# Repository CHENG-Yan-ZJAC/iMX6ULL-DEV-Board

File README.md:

# iMX6ULL-DEV-Board

iMX6ULL-DEV-Board is a development board based on NXP i.MX6ULL. It is composed of core board and carrier board. The boards were developed in KiCad 8.0.

## Core Board
* i.MX6ULL, MCIMX6Y2CVM08AB, ARM Cortex-A7, 798MHz.
* Samsung, KLM8G1GETF-B041, 8GB eMMC.
* Micro, MT41K256M16, DDR3L, 512MB.
* DDR4 edge connector.

## Carrier Board
* micro SD x 1, 4-bit width.
* LCD.
* CSI.
* UART1, UART2.
* USB1: used as power and flash the eMMC.
* USB2: expand to 4 USB Type-A by USB Hub (GENESYS GL850G-HHY22).
* ENET1, ENET2: PHY SMSC LAN8720A-CP-TR.
* GPIO.

## How to use
* Connect the J2 (upright corner marked "Power Download") to 5V by a Type-C line.
* Connect the Type-C (the 2nd Type-C connector marked "UART1") to PC, it is the console.
* Insert micro SD to slot (downright corner marked "micro SD").
* Set the code switch to 1 0 0 0, boot from micro SD.
* Swith on (upright corner marked "ON OFF").

## Contact:
Feel free to contact me yan.cheng@hnautocontrol.com.

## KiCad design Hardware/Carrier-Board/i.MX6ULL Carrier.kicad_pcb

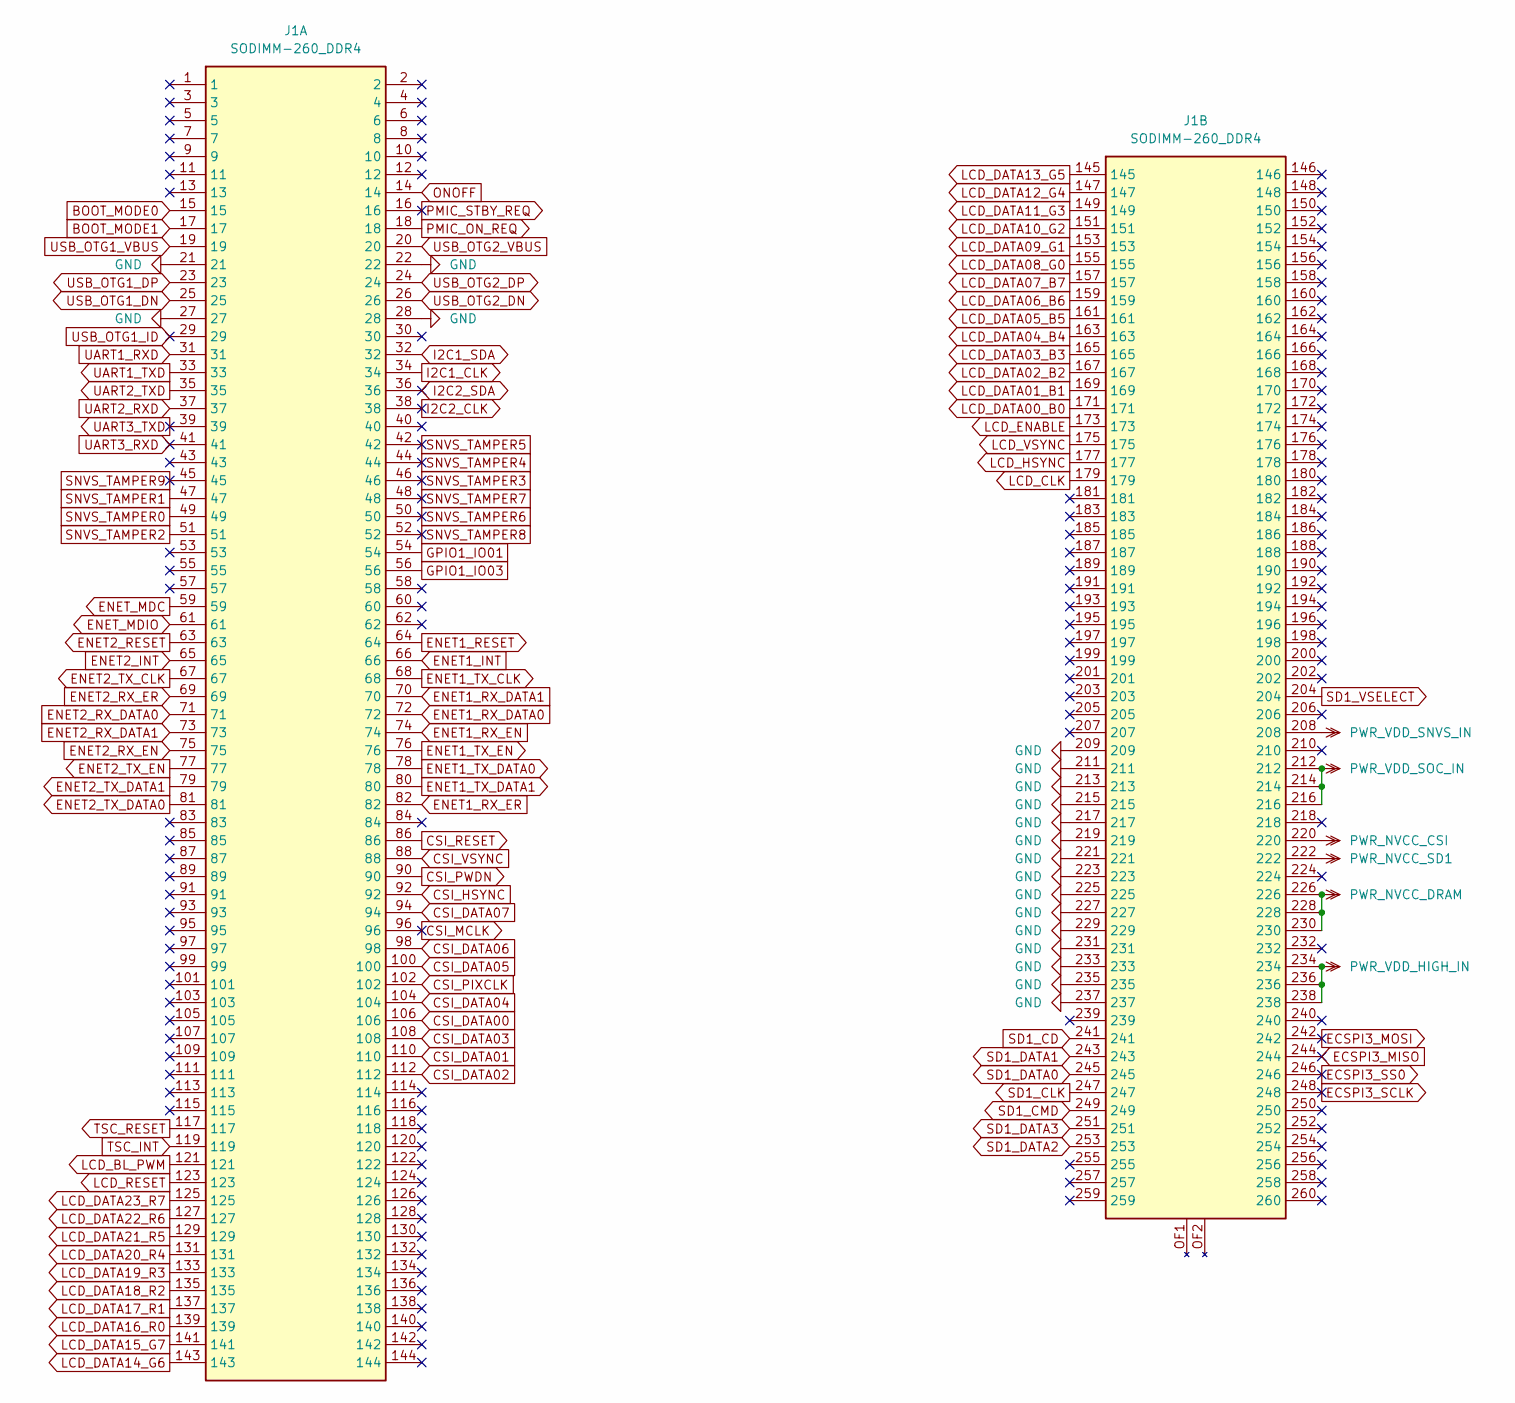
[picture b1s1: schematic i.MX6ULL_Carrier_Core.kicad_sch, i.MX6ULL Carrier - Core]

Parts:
J1: SODIMM-260_DDR4; SODIMM-260_DDR4_Card_slot

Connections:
BOOT_MODE0: J1.15; also elsewhere on the board
BOOT_MODE1: J1.17; also elsewhere on the board
CSI_DATA00: J1.106; also elsewhere on the board
CSI_DATA01: J1.110; also elsewhere on the board
CSI_DATA02: J1.112; also elsewhere on the board
CSI_DATA03: J1.108; also elsewhere on the board
CSI_DATA04: J1.104; also elsewhere on the board
CSI_DATA05: J1.100; also elsewhere on the board
CSI_DATA06: J1.98; also elsewhere on the board
CSI_DATA07: J1.94; also elsewhere on the board
CSI_HSYNC: J1.92; also elsewhere on the board
CSI_MCLK: J1.96
CSI_PIXCLK: J1.102; also elsewhere on the board
CSI_PWDN: J1.90; also elsewhere on the board
CSI_RESET: J1.86; also elsewhere on the board
CSI_VSYNC: J1.88; also elsewhere on the board
ECSPI3_MISO: J1.244
ECSPI3_MOSI: J1.242
ECSPI3_SCLK: J1.248
ECSPI3_SS0: J1.246
ENET1_INT: J1.66; also elsewhere on the board
ENET1_RESET: J1.64; also elsewhere on the board
ENET1_RX_DATA0: J1.72; also elsewhere on the board
ENET1_RX_DATA1: J1.70; also elsewhere on the board
ENET1_RX_EN: J1.74; also elsewhere on the board
ENET1_RX_ER: J1.82; also elsewhere on the board
ENET1_TX_CLK: J1.68; also elsewhere on the board
ENET1_TX_DATA0: J1.78; also elsewhere on the board
ENET1_TX_DATA1: J1.80; also elsewhere on the board
ENET1_TX_EN: J1.76; also elsewhere on the board
ENET2_INT: J1.65; also elsewhere on the board
ENET2_RESET: J1.63; also elsewhere on the board
ENET2_RX_DATA0: J1.71; also elsewhere on the board
ENET2_RX_DATA1: J1.73; also elsewhere on the board
ENET2_RX_EN: J1.75; also elsewhere on the board
ENET2_RX_ER: J1.69; also elsewhere on the board
ENET2_TX_CLK: J1.67; also elsewhere on the board
ENET2_TX_DATA0: J1.81; also elsewhere on the board
ENET2_TX_DATA1: J1.79; also elsewhere on the board
ENET2_TX_EN: J1.77; also elsewhere on the board
ENET_MDC: J1.59; also elsewhere on the board
ENET_MDIO: J1.61; also elsewhere on the board
GND: J1.21, J1.22, J1.27, J1.28, J1.209, J1.211, J1.213, J1.215, J1.217, J1.219, J1.221, J1.223, J1.225, J1.227, J1.229, J1.231, J1.233, J1.235, J1.237; also elsewhere on the board
GPIO1_IO01: J1.54; also elsewhere on the board
GPIO1_IO03: J1.56; also elsewhere on the board
I2C1_CLK: J1.34; also elsewhere on the board
I2C1_SDA: J1.32; also elsewhere on the board
I2C2_CLK: J1.38
I2C2_SDA: J1.36
LCD_BL_PWM: J1.121; also elsewhere on the board
LCD_CLK: J1.179; also elsewhere on the board
LCD_DATA00_B0: J1.171; also elsewhere on the board
LCD_DATA01_B1: J1.169; also elsewhere on the board
LCD_DATA02_B2: J1.167; also elsewhere on the board
LCD_DATA03_B3: J1.165; also elsewhere on the board
LCD_DATA04_B4: J1.163; also elsewhere on the board
LCD_DATA05_B5: J1.161; also elsewhere on the board
LCD_DATA06_B6: J1.159; also elsewhere on the board
LCD_DATA07_B7: J1.157; also elsewhere on the board
LCD_DATA08_G0: J1.155; also elsewhere on the board
LCD_DATA09_G1: J1.153; also elsewhere on the board
LCD_DATA10_G2: J1.151; also elsewhere on the board
LCD_DATA11_G3: J1.149; also elsewhere on the board
LCD_DATA12_G4: J1.147; also elsewhere on the board
LCD_DATA13_G5: J1.145; also elsewhere on the board
LCD_DATA14_G6: J1.143; also elsewhere on the board
LCD_DATA15_G7: J1.141; also elsewhere on the board
LCD_DATA16_R0: J1.139; also elsewhere on the board
LCD_DATA17_R1: J1.137; also elsewhere on the board
LCD_DATA18_R2: J1.135; also elsewhere on the board
LCD_DATA19_R3: J1.133; also elsewhere on the board
LCD_DATA20_R4: J1.131; also elsewhere on the board
LCD_DATA21_R5: J1.129; also elsewhere on the board
LCD_DATA22_R6: J1.127; also elsewhere on the board
LCD_DATA23_R7: J1.125; also elsewhere on the board
LCD_ENABLE: J1.173; also elsewhere on the board
LCD_HSYNC: J1.177; also elsewhere on the board
LCD_RESET: J1.123; also elsewhere on the board
LCD_VSYNC: J1.175; also elsewhere on the board
ONOFF: J1.14; also elsewhere on the board
PMIC_ON_REQ: J1.18; also elsewhere on the board
PMIC_STBY_REQ: J1.16
PWR_NVCC_CSI: J1.220; also elsewhere on the board
PWR_NVCC_DRAM: J1.212, J1.214, J1.216, J1.226, J1.228, J1.230; also elsewhere on the board
PWR_NVCC_SD1: J1.222; also elsewhere on the board
PWR_VDD_HIGH_IN: J1.234, J1.236, J1.238; also elsewhere on the board
PWR_VDD_SNVS_IN: J1.208; also elsewhere on the board
SD1_CD: J1.241; also elsewhere on the board
SD1_CLK: J1.247; also elsewhere on the board
SD1_CMD: J1.249; also elsewhere on the board
SD1_DATA0: J1.245; also elsewhere on the board
SD1_DATA1: J1.243; also elsewhere on the board
SD1_DATA2: J1.253; also elsewhere on the board
SD1_DATA3: J1.251; also elsewhere on the board
SD1_VSELECT: J1.204; also elsewhere on the board
SNVS_TAMPER0: J1.49; also elsewhere on the board
SNVS_TAMPER1: J1.47; also elsewhere on the board
SNVS_TAMPER2: J1.51; also elsewhere on the board
SNVS_TAMPER3: J1.46
SNVS_TAMPER4: J1.44
SNVS_TAMPER5: J1.42
SNVS_TAMPER6: J1.50
SNVS_TAMPER7: J1.48
SNVS_TAMPER8: J1.52
SNVS_TAMPER9: J1.45
TSC_INT: J1.119; also elsewhere on the board
TSC_RESET: J1.117; also elsewhere on the board
UART1_RXD: J1.31; also elsewhere on the board
UART1_TXD: J1.33; also elsewhere on the board
UART2_RXD: J1.37; also elsewhere on the board
UART2_TXD: J1.35; also elsewhere on the board
UART3_RXD: J1.41
UART3_TXD: J1.39
USB_OTG1_DN: J1.25; also elsewhere on the board
USB_OTG1_DP: J1.23; also elsewhere on the board
USB_OTG1_ID: J1.29
USB_OTG1_VBUS: J1.19; also elsewhere on the board
USB_OTG2_DN: J1.26; also elsewhere on the board
USB_OTG2_DP: J1.24; also elsewhere on the board
USB_OTG2_VBUS: J1.20; also elsewhere on the board

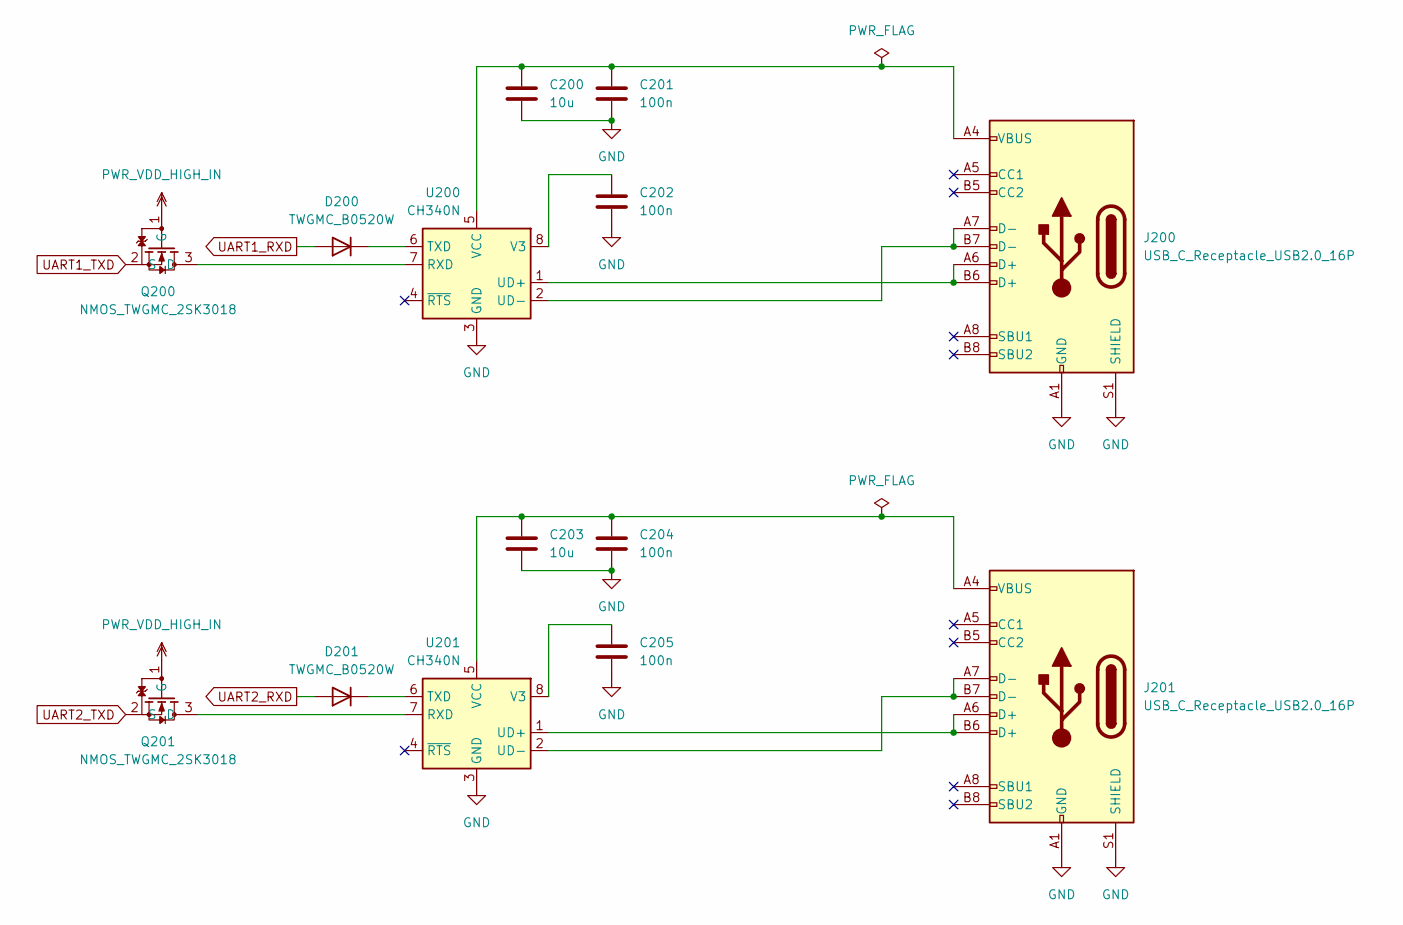
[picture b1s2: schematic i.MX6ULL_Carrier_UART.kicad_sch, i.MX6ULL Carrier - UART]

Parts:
C200, C203: 10u; C_0603_1608Metric
C201, C202, C204, C205: 100n; C_0603_1608Metric
D200, D201: TWGMC_B0520W; D_SOD-123
J200, J201: USB_C_Receptacle_USB2.0_16P; USB_C_Receptacle_G-Switch_GT-USB-7010ASV
Q200, Q201: NMOS_TWGMC_2SK3018; SOT-23-3
U200, U201: CH340N; SOP-8_3.9x4.9mm_P1.27mm

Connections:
GND: C200.2, C201.2, C202.2, C203.2, C204.2, C205.2, J200.A1 (GND), J200.A12 (GND), J200.B1 (GND), J200.B12 (GND), J200.S1 (SHIELD), J201.A1 (GND), J201.A12 (GND), J201.B1 (GND), J201.B12 (GND), J201.S1 (SHIELD), U200.3 (GND), U201.3 (GND); also elsewhere on the board
unnamed: D200.1 (K), U200.6 (TXD)
unnamed: D201.1 (K), U201.6 (TXD)
unnamed: Q200.3 (D), U200.7 (RXD)
unnamed: Q201.3 (D), U201.7 (RXD)
unnamed: J200.A6 (D+), J200.B6 (D+), U200.1 (UD+)
unnamed: J200.A7 (D-), J200.B7 (D-), U200.2 (UD-)
unnamed: C202.1, U200.8 (V3)
unnamed: C200.1, C201.1, J200.A4 (VBUS), J200.A9 (VBUS), J200.B4 (VBUS), J200.B9 (VBUS), U200.5 (VCC)
unnamed: J201.A6 (D+), J201.B6 (D+), U201.1 (UD+)
unnamed: J201.A7 (D-), J201.B7 (D-), U201.2 (UD-)
unnamed: C205.1, U201.8 (V3)
unnamed: C203.1, C204.1, J201.A4 (VBUS), J201.A9 (VBUS), J201.B4 (VBUS), J201.B9 (VBUS), U201.5 (VCC)
PWR_VDD_HIGH_IN: Q200.1 (G), Q201.1 (G); also elsewhere on the board
UART1_RXD: D200.2 (A); also elsewhere on the board
UART1_TXD: Q200.2 (S); also elsewhere on the board
UART2_RXD: D201.2 (A); also elsewhere on the board
UART2_TXD: Q201.2 (S); also elsewhere on the board

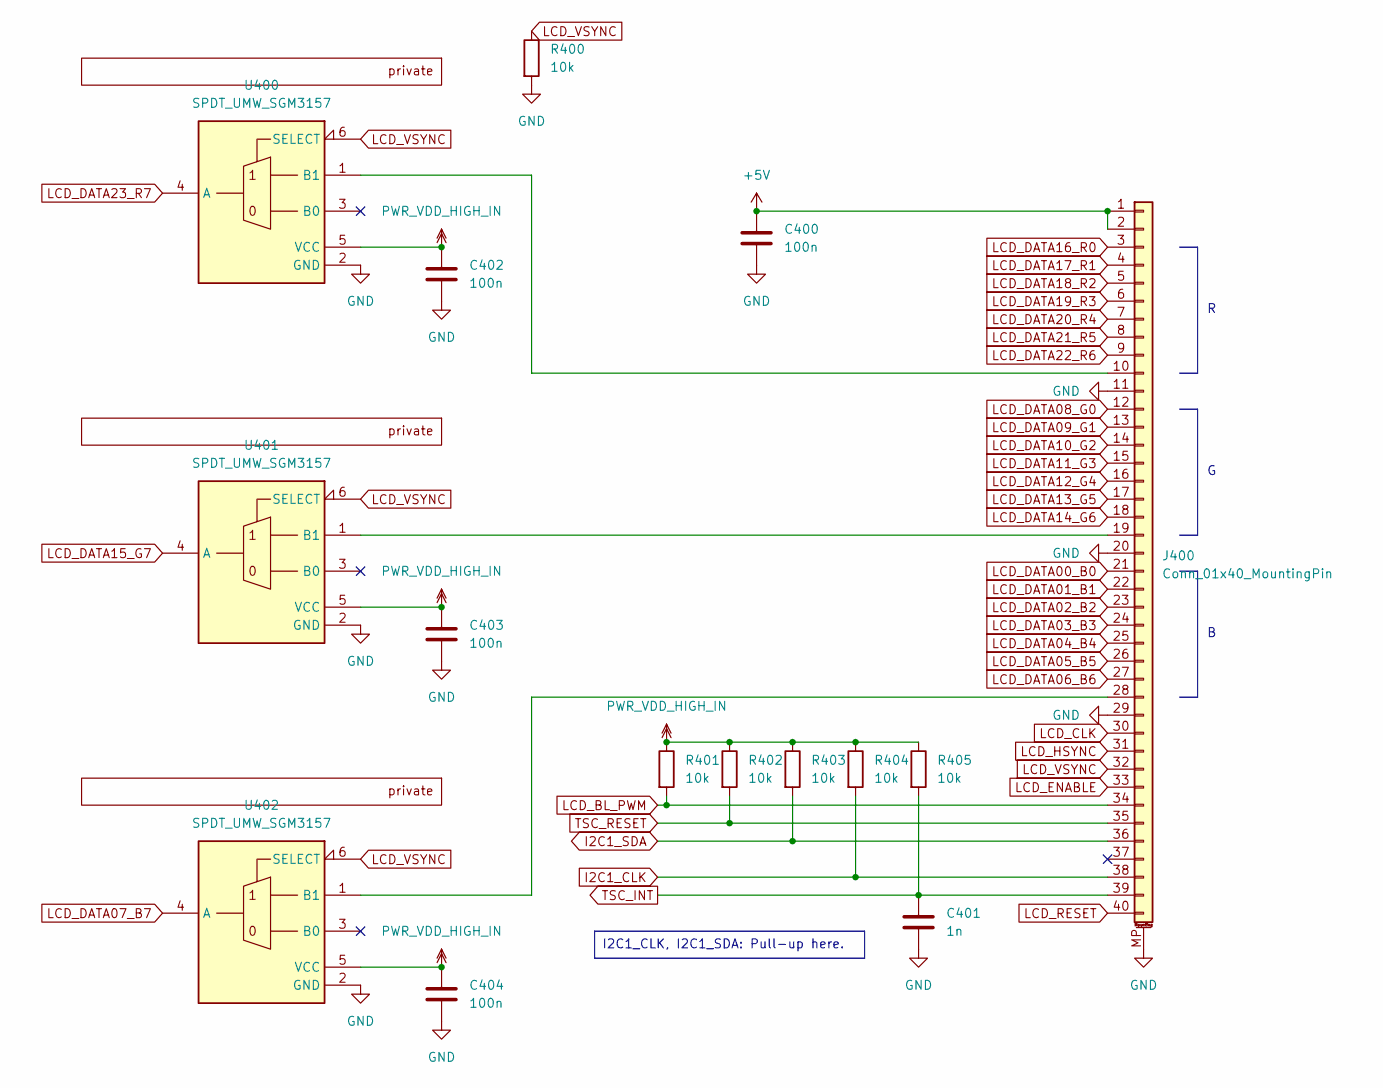
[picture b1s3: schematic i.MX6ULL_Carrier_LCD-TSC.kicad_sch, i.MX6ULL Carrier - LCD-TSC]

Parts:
C400, C402, C403, C404: 100n; C_0603_1608Metric
C401: 1n; C_0603_1608Metric
J400: Conn_01x40_MountingPin; Connector_FPC_1x40-1MP_P0.05mm
R400, R401, R402, R403, R404, R405: 10k; R_0603_1608Metric
U400, U401, U402: SPDT_UMW_SGM3157; SOT-363_SC-70-6

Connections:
+5V: C400.1, J400.1, J400.2; also elsewhere on the board
GND: C400.2, C401.2, C402.2, C403.2, C404.2, J400.11, J400.20, J400.29, J400.MP (MountPin), R400.2, U400.2 (GND), U401.2 (GND), U402.2 (GND); also elsewhere on the board
I2C1_CLK: J400.38, R404.2; also elsewhere on the board
I2C1_SDA: J400.36, R403.2; also elsewhere on the board
LCD_BL_PWM: J400.34, R401.2; also elsewhere on the board
LCD_CLK: J400.30; also elsewhere on the board
LCD_DATA00_B0: J400.21; also elsewhere on the board
LCD_DATA01_B1: J400.22; also elsewhere on the board
LCD_DATA02_B2: J400.23; also elsewhere on the board
LCD_DATA03_B3: J400.24; also elsewhere on the board
LCD_DATA04_B4: J400.25; also elsewhere on the board
LCD_DATA05_B5: J400.26; also elsewhere on the board
LCD_DATA06_B6: J400.27; also elsewhere on the board
LCD_DATA07_B7: U402.4 (A); also elsewhere on the board
LCD_DATA08_G0: J400.12; also elsewhere on the board
LCD_DATA09_G1: J400.13; also elsewhere on the board
LCD_DATA10_G2: J400.14; also elsewhere on the board
LCD_DATA11_G3: J400.15; also elsewhere on the board
LCD_DATA12_G4: J400.16; also elsewhere on the board
LCD_DATA13_G5: J400.17; also elsewhere on the board
LCD_DATA14_G6: J400.18; also elsewhere on the board
LCD_DATA15_G7: U401.4 (A); also elsewhere on the board
LCD_DATA16_R0: J400.3; also elsewhere on the board
LCD_DATA17_R1: J400.4; also elsewhere on the board
LCD_DATA18_R2: J400.5; also elsewhere on the board
LCD_DATA19_R3: J400.6; also elsewhere on the board
LCD_DATA20_R4: J400.7; also elsewhere on the board
LCD_DATA21_R5: J400.8; also elsewhere on the board
LCD_DATA22_R6: J400.9; also elsewhere on the board
LCD_DATA23_R7: U400.4 (A); also elsewhere on the board
LCD_ENABLE: J400.33; also elsewhere on the board
LCD_HSYNC: J400.31; also elsewhere on the board
LCD_RESET: J400.40; also elsewhere on the board
LCD_VSYNC: J400.32, R400.1, U400.6 (SELECT), U401.6 (SELECT), U402.6 (SELECT); also elsewhere on the board
unnamed: J400.10, U400.1 (B1)
unnamed: J400.19, U401.1 (B1)
unnamed: J400.28, U402.1 (B1)
PWR_VDD_HIGH_IN: C402.1, C403.1, C404.1, R401.1, R402.1, R403.1, R404.1, R405.1, U400.5 (VCC), U401.5 (VCC), U402.5 (VCC); also elsewhere on the board
TSC_INT: C401.1, J400.39, R405.2; also elsewhere on the board
TSC_RESET: J400.35, R402.2; also elsewhere on the board

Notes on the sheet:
I2C1_CLK, I2C1_SDA: Pull-up here.

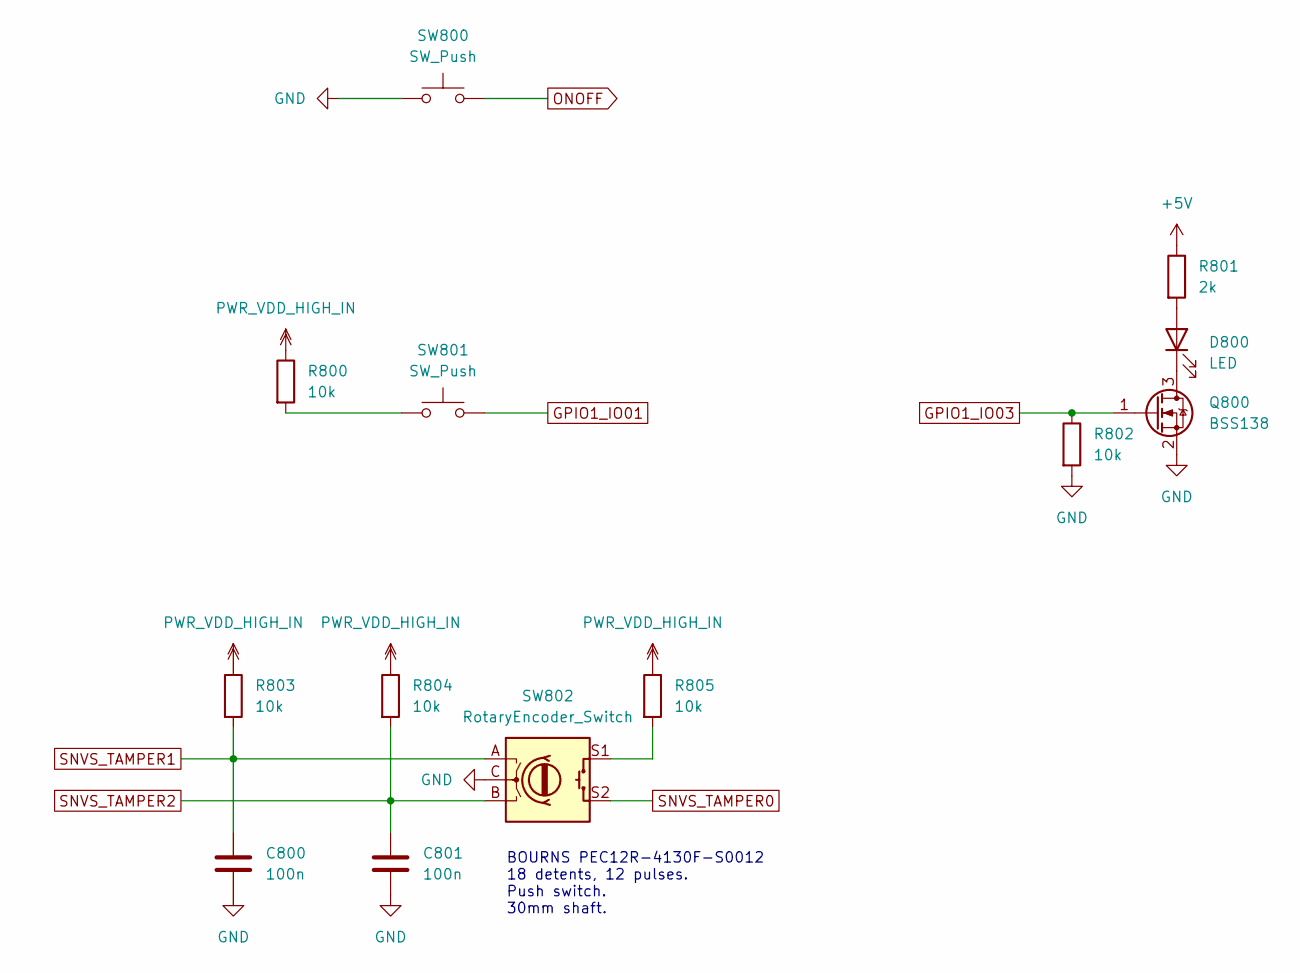
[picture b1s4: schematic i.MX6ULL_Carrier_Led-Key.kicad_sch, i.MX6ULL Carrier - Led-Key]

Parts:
C800, C801: 100n; C_0603_1608Metric
D800: LED; LED_1206_3216Metric
Q800: BSS138; SOT-23-3
R800, R802, R803, R804, R805: 10k; R_0603_1608Metric
R801: 2k; R_1206_3216Metric
SW800, SW801: SW_Push; SW_PUSH_6mm
SW802: RotaryEncoder_Switch; RotaryEncoder_Bourns_Vertical_PEC12R-3x17F-Sxxxx

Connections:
+5V: R801.1; also elsewhere on the board
GND: C800.2, C801.2, Q800.2 (S), R802.2, SW800.1, SW802.C; also elsewhere on the board
GPIO1_IO01: SW801.2; also elsewhere on the board
GPIO1_IO03: Q800.1 (G), R802.1; also elsewhere on the board
unnamed: D800.2 (A), R801.2
unnamed: D800.1 (K), Q800.3 (D)
unnamed: R800.2, SW801.1
unnamed: R805.2, SW802.S1
ONOFF: SW800.2; also elsewhere on the board
PWR_VDD_HIGH_IN: R800.1, R803.1, R804.1, R805.1; also elsewhere on the board
SNVS_TAMPER0: SW802.S2; also elsewhere on the board
SNVS_TAMPER1: C800.1, R803.2, SW802.A; also elsewhere on the board
SNVS_TAMPER2: C801.1, R804.2, SW802.B; also elsewhere on the board

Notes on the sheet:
BOURNS PEC12R-4130F-S0012 18 detents, 12 pulses. Push switch. 30mm shaft.

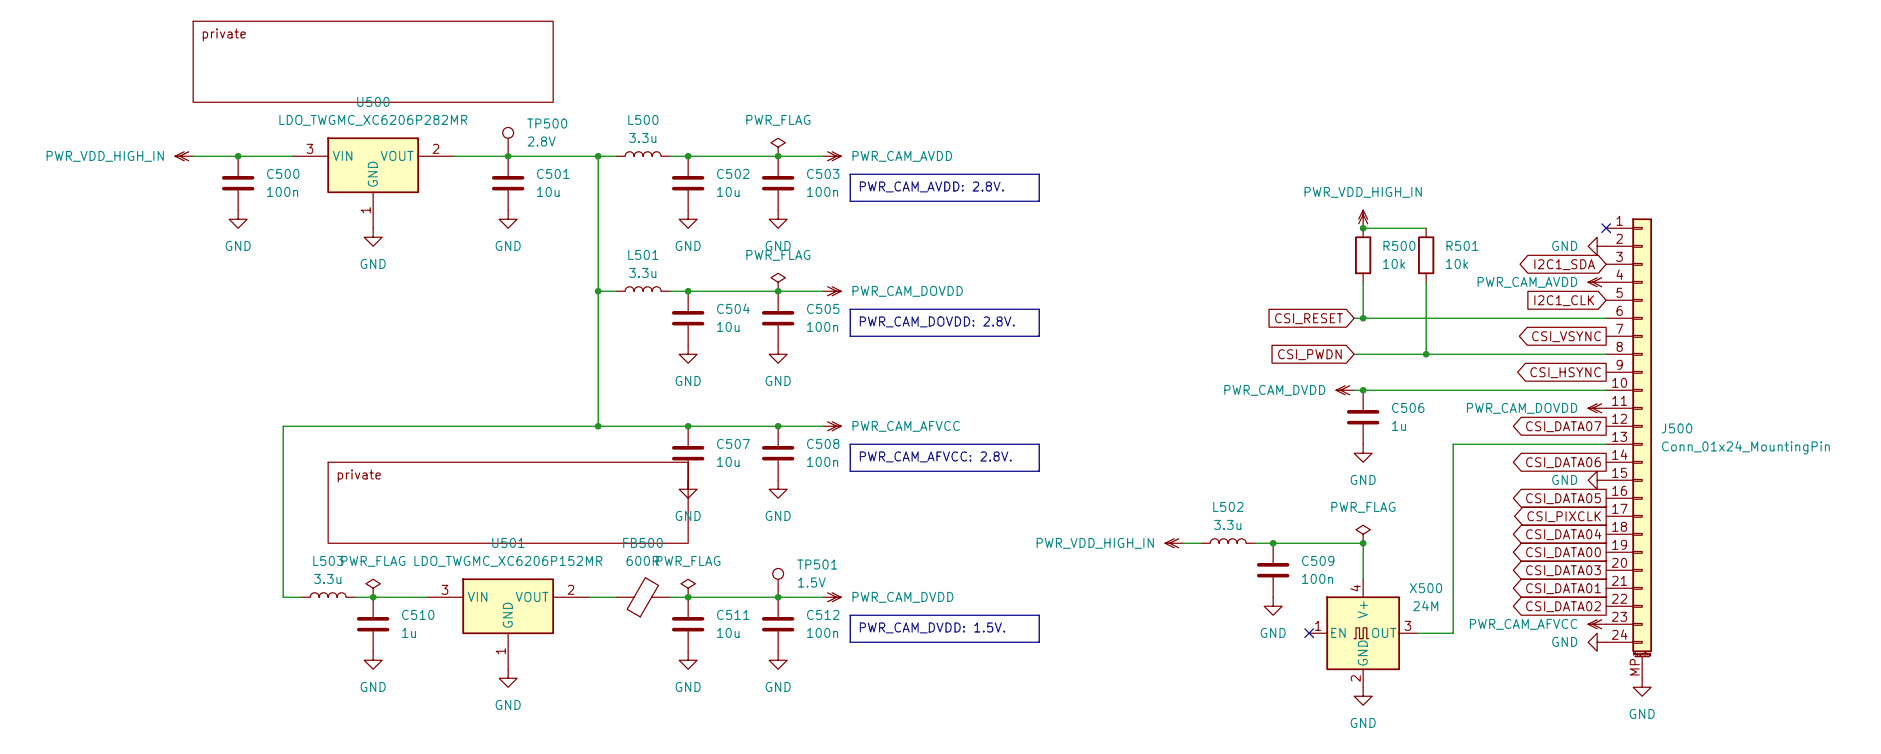
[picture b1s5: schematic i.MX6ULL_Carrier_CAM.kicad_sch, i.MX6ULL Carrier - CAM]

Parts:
C500, C503, C505, C508, C509, C512: 100n; C_0603_1608Metric
C501, C502, C504, C507, C511: 10u; C_0603_1608Metric
C506, C510: 1u; C_0603_1608Metric
FB500: 600R; L_0603_1608Metric
J500: Conn_01x24_MountingPin; Connector_FPC_1x24-1MP_P0.05mm
L500, L501, L502, L503: 3.3u; L_0603_1608Metric
R500, R501: 10k; R_0603_1608Metric
TP500: 2.8V; TestPoint_Pad_D1.0mm
TP501: 1.5V; TestPoint_Pad_D1.0mm
U500: LDO_TWGMC_XC6206P282MR; SOT-23-3
U501: LDO_TWGMC_XC6206P152MR; SOT-23-3
X500: 24M; Oscillator_SMD_EuroQuartz_XO32-4Pin_3.2x2.5mm

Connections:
CSI_DATA00: J500.19; also elsewhere on the board
CSI_DATA01: J500.21; also elsewhere on the board
CSI_DATA02: J500.22; also elsewhere on the board
CSI_DATA03: J500.20; also elsewhere on the board
CSI_DATA04: J500.18; also elsewhere on the board
CSI_DATA05: J500.16; also elsewhere on the board
CSI_DATA06: J500.14; also elsewhere on the board
CSI_DATA07: J500.12; also elsewhere on the board
CSI_HSYNC: J500.9; also elsewhere on the board
CSI_PIXCLK: J500.17; also elsewhere on the board
CSI_PWDN: J500.8, R501.2; also elsewhere on the board
CSI_RESET: J500.6, R500.2; also elsewhere on the board
CSI_VSYNC: J500.7; also elsewhere on the board
GND: C500.2, C501.2, C502.2, C503.2, C504.2, C505.2, C506.2, C507.2, C508.2, C509.2, C510.2, C511.2, C512.2, J500.2, J500.15, J500.24, J500.MP (MountPin), U500.1 (GND), U501.1 (GND), X500.2 (GND); also elsewhere on the board
I2C1_CLK: J500.5; also elsewhere on the board
I2C1_SDA: J500.3; also elsewhere on the board
unnamed: J500.13, X500.3 (OUT)
unnamed: C510.1, L503.2, U501.3 (VIN)
unnamed: FB500.1, U501.2 (VOUT)
unnamed: C509.1, L502.2, X500.4 (V+)
PWR_CAM_AFVCC: C501.1, C507.1, C508.1, J500.23, L500.1, L501.1, L503.1, TP500.1, U500.2 (VOUT)
PWR_CAM_AVDD: C502.1, C503.1, J500.4, L500.2
PWR_CAM_DOVDD: C504.1, C505.1, J500.11, L501.2
PWR_CAM_DVDD: C506.1, C511.1, C512.1, FB500.2, J500.10, TP501.1
PWR_VDD_HIGH_IN: C500.1, L502.1, R500.1, R501.1, U500.3 (VIN); also elsewhere on the board

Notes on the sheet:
PWR_CAM_DVDD: 1.5V.
PWR_CAM_AFVCC: 2.8V.
PWR_CAM_AVDD: 2.8V.
PWR_CAM_DOVDD: 2.8V.

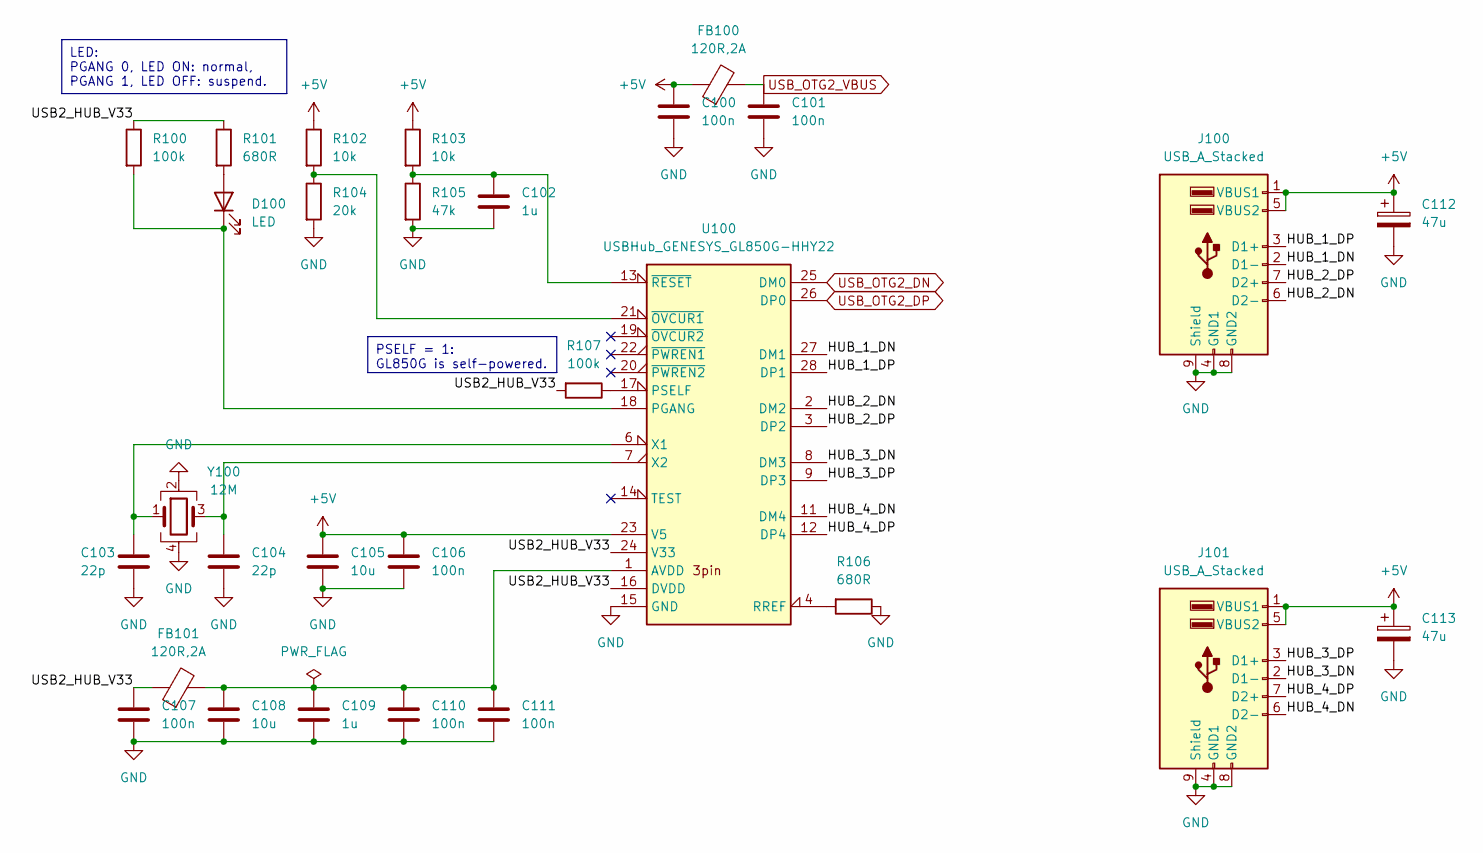
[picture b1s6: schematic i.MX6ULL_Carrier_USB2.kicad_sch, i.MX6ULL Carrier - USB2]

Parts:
C100, C101, C106, C107, C110, C111: 100n; C_0603_1608Metric
C102, C109: 1u; C_0603_1608Metric
C103, C104: 22p; C_0603_1608Metric
C105, C108: 10u; C_0603_1608Metric
C112, C113: 47u; CP_Elec_6.3x5.4
D100: LED; LED_1206_3216Metric
FB100, FB101: 120R,2A; L_0603_1608Metric
J100, J101: USB_A_Stacked; USB_A_CUI_UJ2-ADH-TH_Horizontal_Stacked
R100, R107: 100k; R_0603_1608Metric
R101, R106: 680R; R_0603_1608Metric
R102, R103: 10k; R_0603_1608Metric
R104: 20k; R_0603_1608Metric
R105: 47k; R_0603_1608Metric
U100: USBHub_GENESYS_GL850G-HHY22; SSOP-28_5.3x10.2mm_P0.65mm
Y100: 12M; Crystal_SMD_3225-4Pin_3.2x2.5mm

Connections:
+5V: C100.1, C105.1, C106.1, C112.1, C113.1, FB100.1, J100.1 (VBUS1), J100.5 (VBUS2), J101.1 (VBUS1), J101.5 (VBUS2), R102.1, R103.1, U100.23 (V5); also elsewhere on the board
/USB2/HUB_1_DN: J100.2 (D1-), U100.27 (DM1)
/USB2/HUB_1_DP: J100.3 (D1+), U100.28 (DP1)
/USB2/HUB_2_DN: J100.6 (D2-), U100.2 (DM2)
/USB2/HUB_2_DP: J100.7 (D2+), U100.3 (DP2)
/USB2/HUB_3_DN: J101.2 (D1-), U100.8 (DM3)
/USB2/HUB_3_DP: J101.3 (D1+), U100.9 (DP3)
/USB2/HUB_4_DN: J101.6 (D2-), U100.11 (DM4)
/USB2/HUB_4_DP: J101.7 (D2+), U100.12 (DP4)
/USB2/USB2_HUB_V33: C107.1, FB101.1, R100.1, R101.1, R107.2, U100.16 (DVDD), U100.24 (V33)
GND: C100.2, C101.2, C102.2, C103.2, C104.2, C105.2, C106.2, C107.2, C108.2, C109.2, C110.2, C111.2, C112.2, C113.2, J100.4 (GND1), J100.8 (GND2), J100.9 (Shield), J101.4 (GND1), J101.8 (GND2), J101.9 (Shield), R104.2, R105.2, R106.1, U100.15 (GND), Y100.2, Y100.4; also elsewhere on the board
unnamed: C108.1, C109.1, C110.1, C111.1, FB101.2, U100.1 (AVDD), U100.5 (AVDD), U100.10 (AVDD)
unnamed: D100.2 (A), R101.2
unnamed: D100.1 (K), R100.2, U100.18 (PGANG)
unnamed: R107.1, U100.17 (PSELF)
unnamed: R106.2, U100.4 (RREF)
unnamed: C103.1, U100.6 (X1), Y100.1
unnamed: C104.1, U100.7 (X2), Y100.3
unnamed: R102.2, R104.1, U100.21 (~OVCUR1)
unnamed: C102.1, R103.2, R105.1, U100.13 (~RESET)
USB_OTG2_DN: U100.25 (DM0); also elsewhere on the board
USB_OTG2_DP: U100.26 (DP0); also elsewhere on the board
USB_OTG2_VBUS: C101.1, FB100.2; also elsewhere on the board

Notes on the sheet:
PSELF = 1: GL850G is self-powered.
LED: PGANG 0, LED ON: normal, PGANG 1, LED OFF: suspend.
